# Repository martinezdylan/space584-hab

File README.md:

# space584-hab
A repository for the UM squad in SPACE 584 for High Altitude Baloon (Team KGB - Kewl Girls and Boiz).

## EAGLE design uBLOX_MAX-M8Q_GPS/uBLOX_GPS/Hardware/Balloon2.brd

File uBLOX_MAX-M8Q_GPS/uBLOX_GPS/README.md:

# Balloon Mission Computer 4

Ido Roseman

bmc4 is an attemp to use the Raspberry Pi as a mission computer for high altitude balloons.
this is a work in progress so documentation is minimal and bugs galor

## You can find me at
idoroseman.com
ido.roseman@gmail.com

## contribution
more code is needed. you are welcome to participate

## License
All of the code contained here is licensed by T.B.D

## Credits

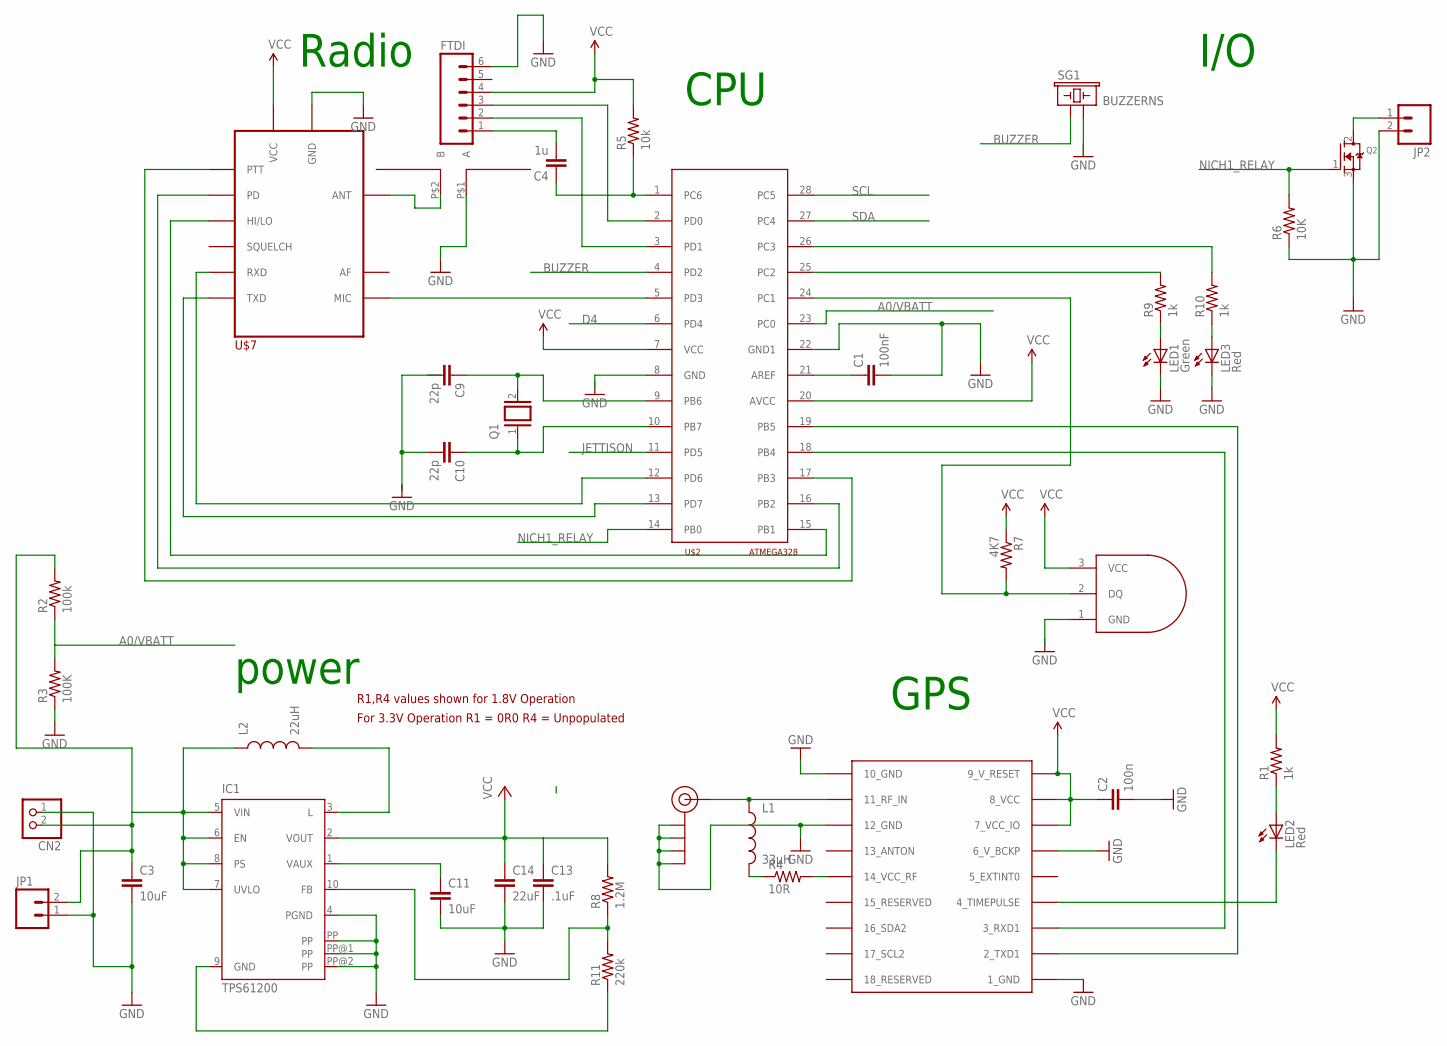
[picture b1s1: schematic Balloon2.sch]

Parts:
C1: 100nF; 0805
C2: 100n; 0805
C3, C11: 10uF; 0805
C4: 1u; 0805
C9, C10: 22p; 0805
C13: .1uF; 0805
C14: 22uF; 0805
CN2: JST_2PIN-SMT-RA; JST-PH-2-SMT-RA
FTDI: M06SIP; 1X06
IC1: TPS61200; S-PDSO-N10
J$2: SMA_EDGE; SMA-EDGE
JP1, JP2: M02PTH; 1X02
L1: 33µH; 0805
L2: 22uH; INDUCTOR-SRP4020
LED1: Green; CHIP-LED0805
LED2, LED3: Red; CHIP-LED0805
Q1: XTAL/S; QS
Q2: MOSFET-NGDS_TO220V; TO220V
R1, R9, R10: 1k; 0805
R2: 100k; 0805
R3: 100K; 0805
R4: 10R; 0805
R5: 10k; 0805
R6: 10K; 0805
R7: 4K7; 0805
R8: 1.2M; 0805
R11: 220k; 0805
SG1: BUZZERNS; BUZZER-12MM-NS
U$1: UBLOX_MAX
U$2: ATMEGA328; DIL28
U$3: DS18B20; TO-92
U$4: SOLDER-DIPOLE; SOLDERED-DIPOLE-5MM
U$7: DORJI

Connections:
A0/VBATT: R2.1, R3.2, U$2.23 (PC0)
BUZZER: SG1.+ (1), U$2.4 (PD2)
D4: U$2.6 (PD4)
GND: C1.2, C2.2, C3.2, C11.2, C13.2, C14.2, CN2.1 (2), FTDI.6, IC1.4 (PGND), IC1.PP, IC1.PP@1 (PP), IC1.PP@2 (PP), J$2.GND@0 (GND), J$2.GND@1 (GND), J$2.GND@2 (GND), J$2.GND@3 (GND), JP1.1, JP2.2, LED1.C, LED3.C, Q2.3 (S), R3.1, R6.1, U$1.1_GND, U$1.6_V_BCKP, U$1.10_GND, U$1.12_GND, U$2.22 (GND1), U$4.P$1 (A), U$7.P$9 (GND), U$7.P$10 (GND)
JETTISON: U$2.11 (PD5)
unnamed: U$2.5 (PD3), U$7.P$18 (MIC)
unnamed: C4.2, FTDI.1
unnamed: C4.1, R5.1, U$2.1 (PC6)
unnamed: J$2.SIG (SIGNAL), L1.1, U$1.11_RF_IN
unnamed: IC1.3 (L), L2.P$2 (2)
unnamed: U$4.P$2 (B), U$7.P$12 (ANT)
unnamed: LED2.A, R1.1
unnamed: FTDI.3, U$2.2 (PD0)
unnamed: FTDI.2, U$2.3 (PD1)
unnamed: LED2.C, U$1.4_TIMEPULSE
unnamed: LED1.A, R9.1
unnamed: LED3.A, R10.1
unnamed: L1.2, R4.1
unnamed: R4.2, U$1.14_VCC_RF
unnamed: C9.1, Q1.2, U$2.9 (PB6)
unnamed: C10.1, Q1.1, U$2.10 (PB7)
unnamed: U$1.3_RXD1, U$2.18 (PB4)
unnamed: U$2.12 (PD6), U$7.P$16 (RXD)
unnamed: U$2.13 (PD7), U$7.P$17 (TXD)
unnamed: U$2.15 (PB1), U$7.P$7 (HI/LO)
unnamed: U$2.16 (PB2), U$7.P$6 (PD)
unnamed: U$2.17 (PB3), U$7.P$5 (PTT)
unnamed: C3.1, CN2.2 (1), IC1.5 (VIN), IC1.6 (EN), IC1.7 (UVLO), IC1.8 (PS), JP1.2, L2.P$1 (1), R2.2
unnamed: C1.1, U$2.21 (AREF)
unnamed: U$1.2_TXD1, U$2.19 (PB5)
unnamed: R10.2, U$2.26 (PC3)
unnamed: R9.2, U$2.25 (PC2)
unnamed: R7.2, U$2.24 (PC1), U$3.2 (DQ)
unnamed: JP2.1, Q2.2 (D)
unnamed: IC1.10 (FB), R8.1, R11.2
unnamed: C11.1, IC1.1 (VAUX)
unnamed: IC1.9 (GND), R11.1
NICH1_RELAY: Q2.1 (G), R6.2, U$2.14 (PB0)
SCL: U$2.28 (PC5)
SDA: U$2.27 (PC4)
VCC: C2.1, C13.1, C14.1, FTDI.4, IC1.2 (VOUT), R1.2, R5.2, R7.1, R8.2, U$1.7_VCC_IO, U$1.8_VCC, U$1.9_V_RESET, U$2.7 (VCC), U$2.20 (AVCC), U$3.3 (VCC), U$7.P$8 (VCC)

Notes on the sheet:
R1,R4 values shown for 1.8V Operation
For 3.3V Operation R1 = 0R0 R4 = Unpopulated
GPS
Radio
power
CPU
I/O

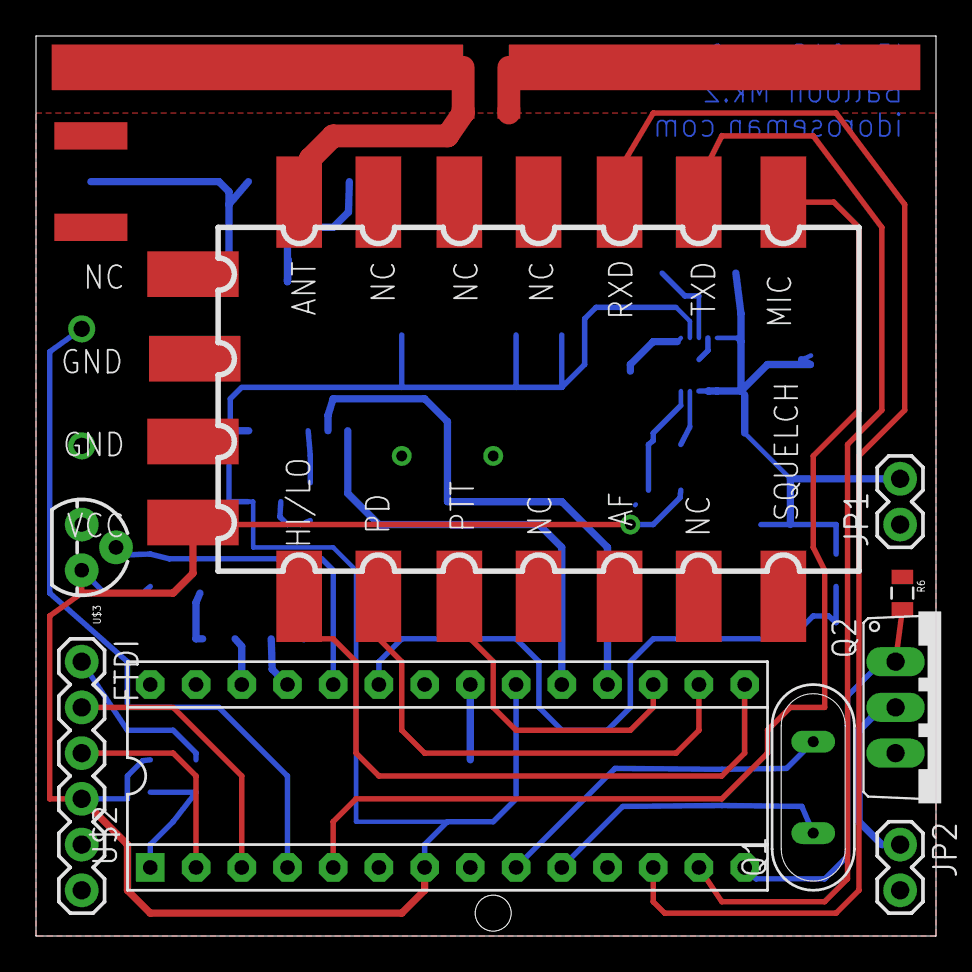
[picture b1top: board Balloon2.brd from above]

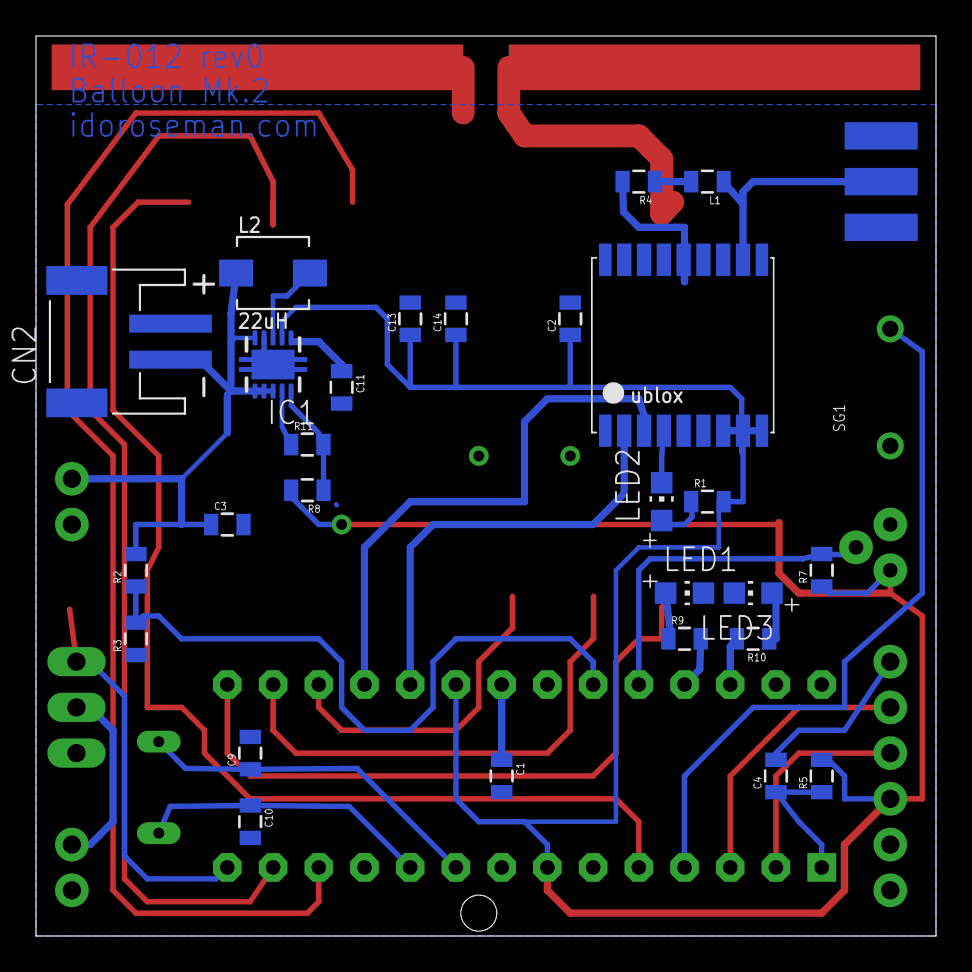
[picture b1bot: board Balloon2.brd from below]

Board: 2 copper layers, 50.0 x 50.0 mm, 39 parts (29 on the bottom side), 37 nets.

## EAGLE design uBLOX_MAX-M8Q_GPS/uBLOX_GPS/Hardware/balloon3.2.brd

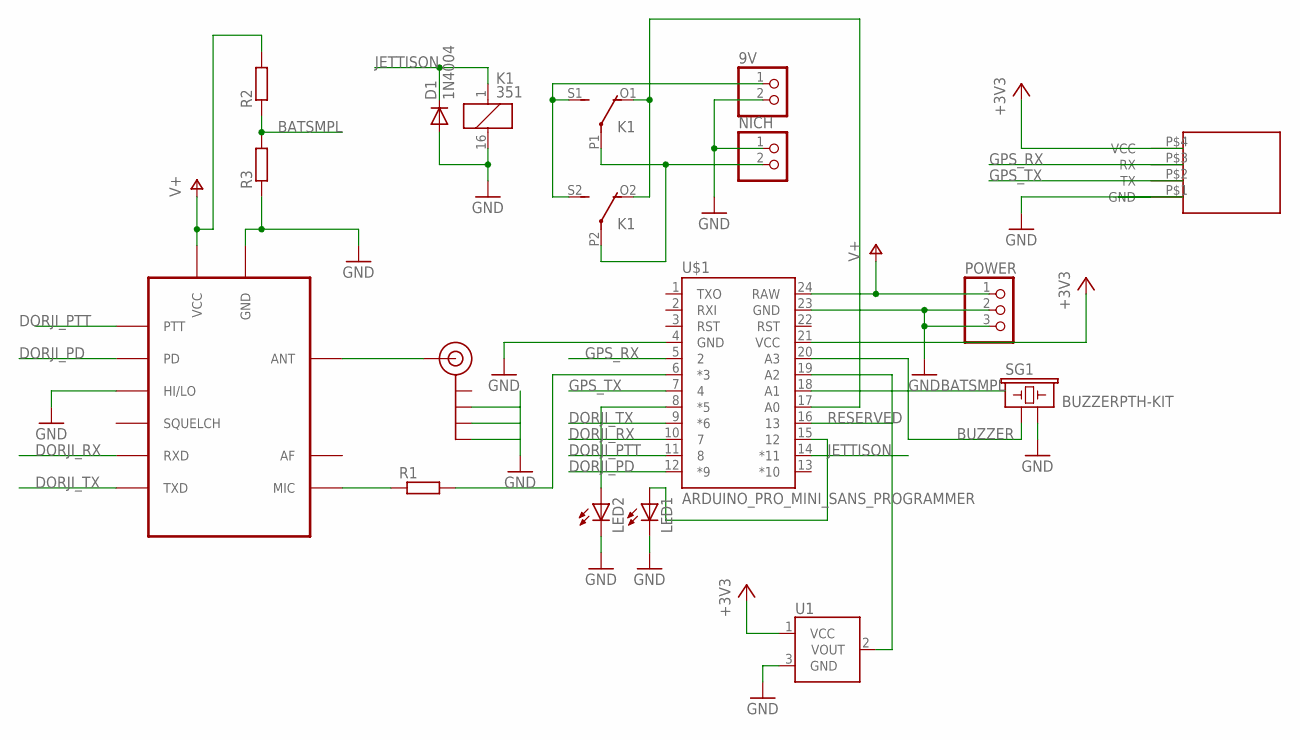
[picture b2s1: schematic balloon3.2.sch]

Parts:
9V: PINHD-1X2; 1X02
D1: 1N4004; DO41-10
J$1: SMA_EDGE; SMA-EDGE
K1: 351
LED1, LED2: LED3MM
NICH: PINHD-1X2; 1X02
POWER: PINHD-1X3; 1X03
R1, R2, R3: R-EU_0204/7; 0204/7
SG1: BUZZERPTH-KIT; BUZZER-12MM-KIT
U1: TMP36GT9; TO-92
U$1: ARDUINO_PRO_MINI_SANS_PROGRAMMER; ARDUINO_PRO_MINI
U$2: DORJI
U$3: NEO-6M-MODULE

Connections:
+3V3: U1.1 (VCC), U$1.21 (VCC), U$3.P$4 (VCC)
BATSMPL: R2.1, R3.2, U$1.18 (A1)
BUZZER: SG1.+ (1), U$1.20 (A3)
DORJI_PD: U$1.12 (*9), U$2.P$6 (PD)
DORJI_PTT: U$1.11 (8), U$2.P$5 (PTT)
DORJI_RX: U$1.10 (7), U$2.P$16 (RXD)
DORJI_TX: U$1.9 (*6), U$2.P$17 (TXD)
GND: 9V.2, D1.A, J$1.GND@1 (GND), J$1.GND@2 (GND), J$1.GND@3 (GND), K1.16 (2), LED1.K (C), LED2.K (C), NICH.1, POWER.2, POWER.3, R3.1, SG1.- (2), U1.3 (GND), U$1.4 (GND), U$1.23 (GND), U$2.P$7 (HI/LO), U$2.P$9 (GND), U$2.P$10 (GND), U$3.P$1 (GND)
GPS_RX: U$1.5 (2), U$3.P$3 (RX)
GPS_TX: U$1.7 (4), U$3.P$2 (TX)
JETTISON: D1.C, K1.1, U$1.14 (*11)
unnamed: R1.2, U$1.6 (*3)
unnamed: R1.1, U$2.P$18 (MIC)
unnamed: J$1.SIG (SIGNAL), U$2.P$12 (ANT)
unnamed: K1.P1, K1.P2, NICH.2
unnamed: LED2.A, U$1.8 (*5)
unnamed: 9V.1, K1.S1 (S), K1.S2 (S)
unnamed: K1.O1 (O), K1.O2 (O), U$1.17 (A0)
unnamed: U1.2 (VOUT), U$1.19 (A2)
unnamed: LED1.A, U$1.15 (12)
RESERVED: U$1.16 (13)
V+: POWER.1, R2.2, U$1.24 (RAW), U$2.P$8 (VCC)

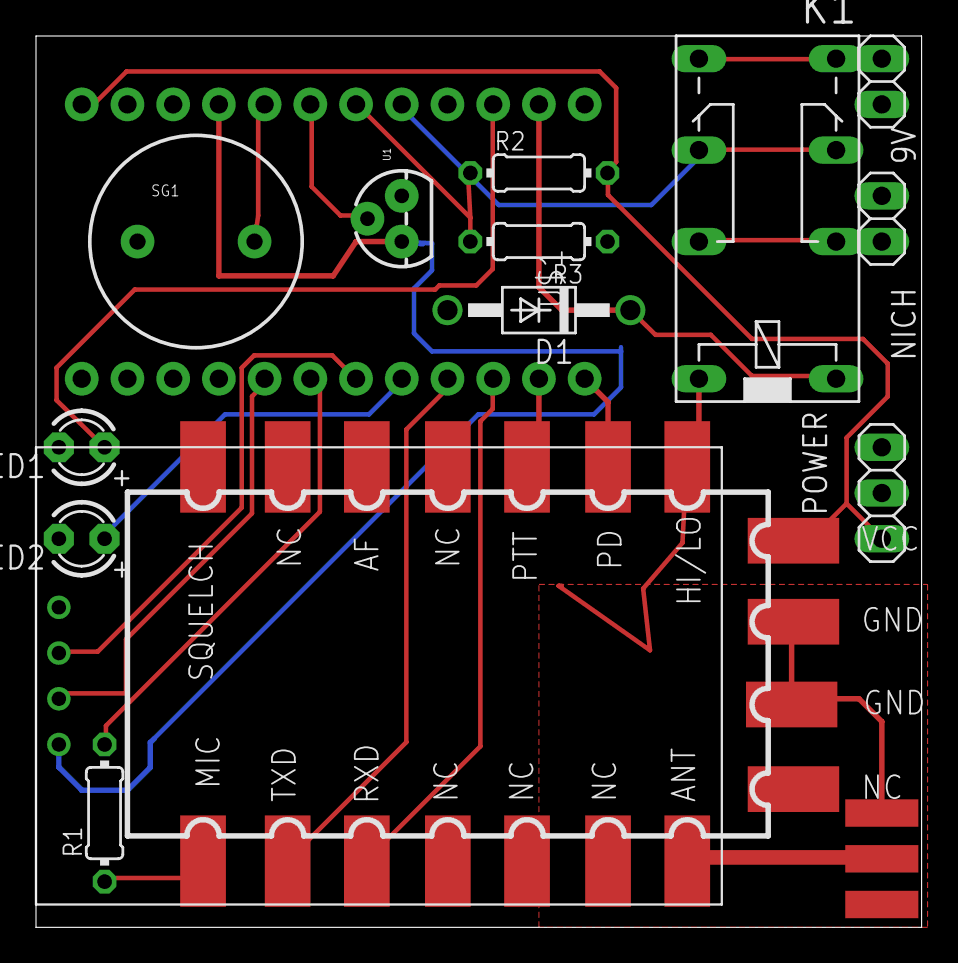
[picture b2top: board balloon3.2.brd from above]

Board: 2 copper layers, 49.2 x 49.5 mm, 16 parts (0 on the bottom side), 21 nets.

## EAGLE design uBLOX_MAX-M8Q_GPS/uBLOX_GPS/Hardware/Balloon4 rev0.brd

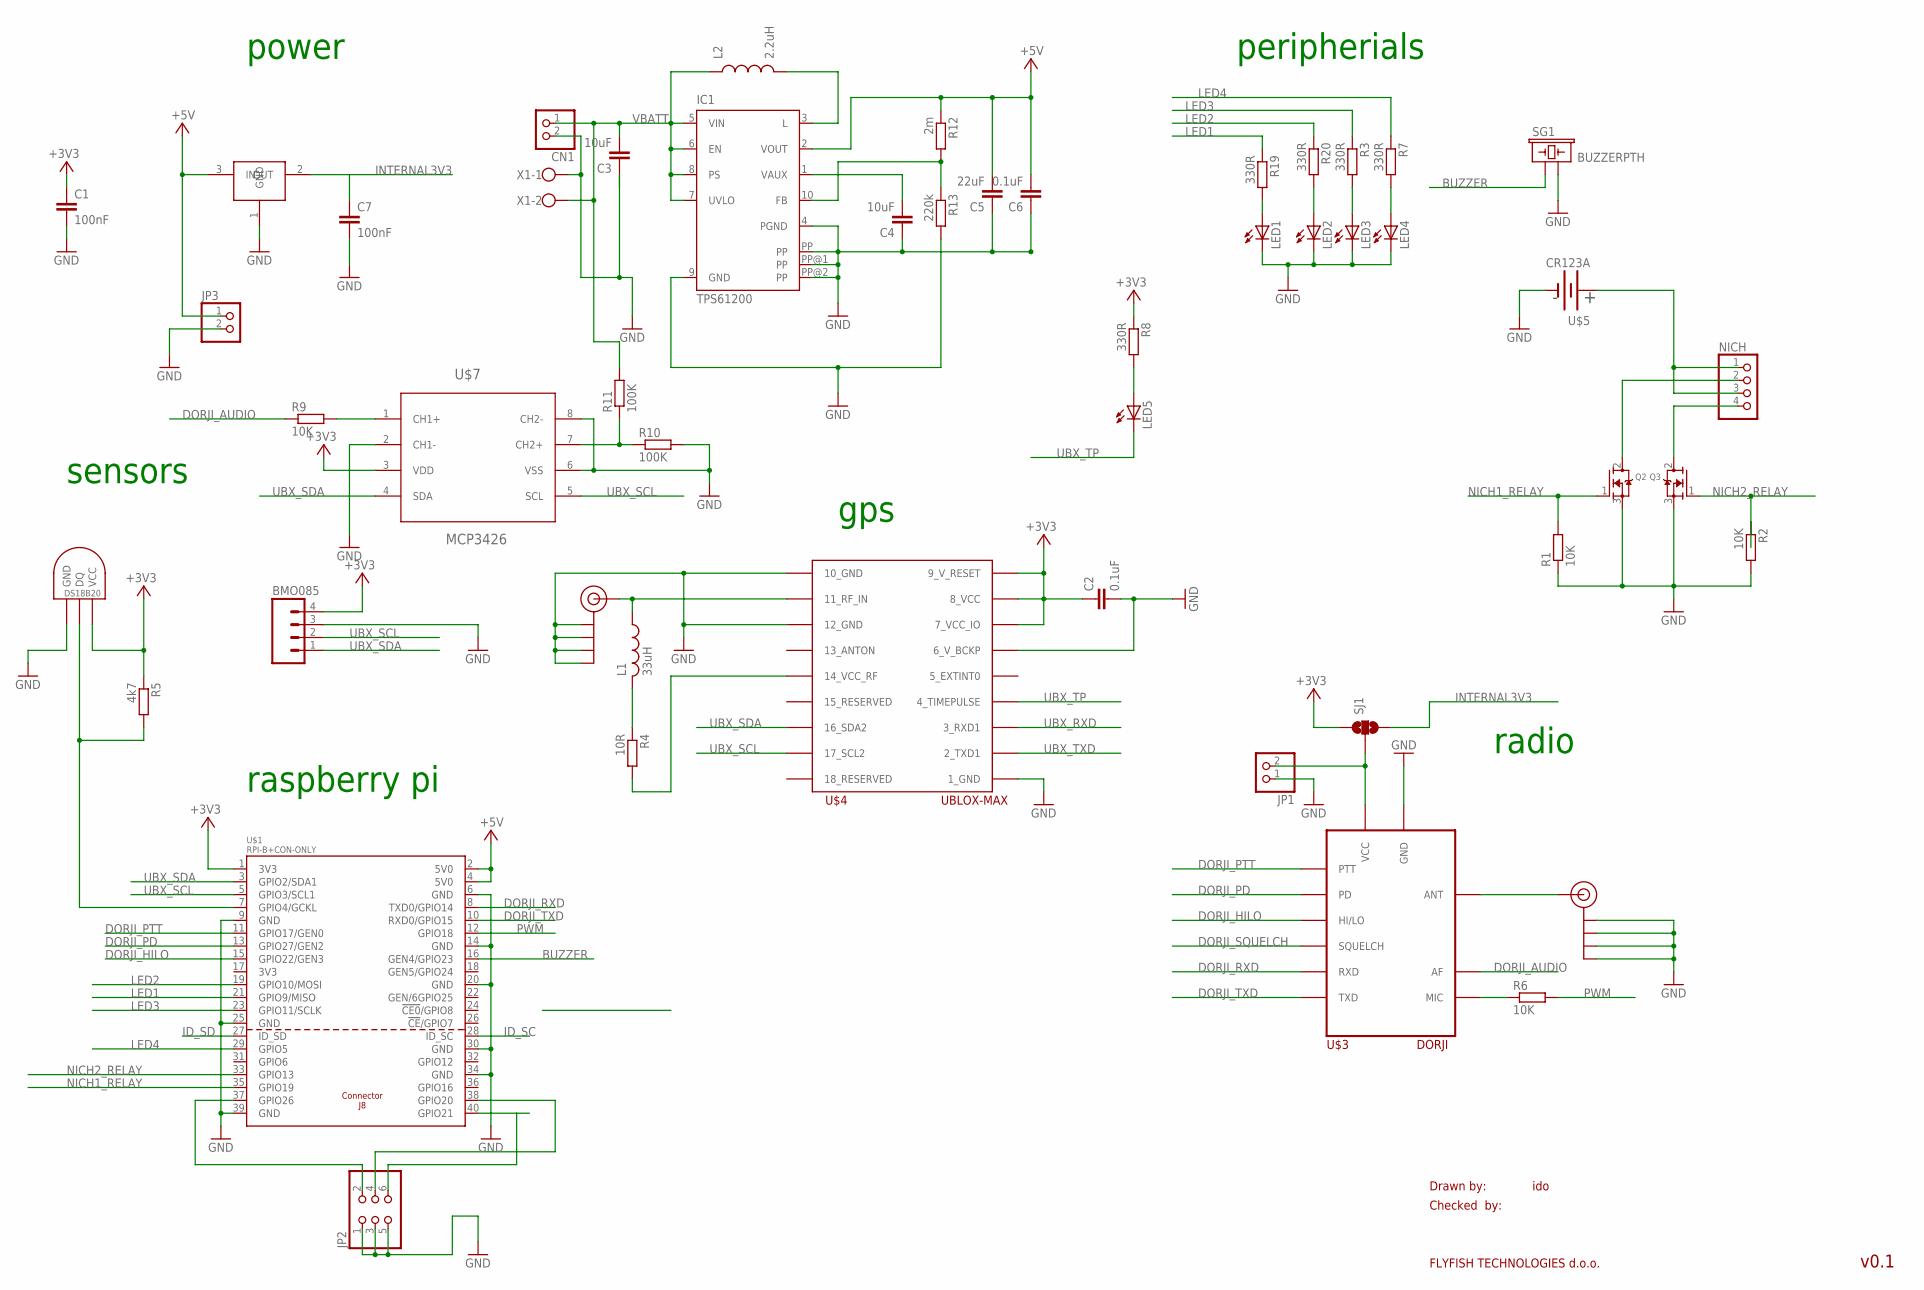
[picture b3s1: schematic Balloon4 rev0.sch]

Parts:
BMO085: M04PTH; 1X04
C1, C7: 100nF; C0805K
C2, C6: 0.1uF; C0805K
C3, C4: 10uF; C0805K
C5: 22uF; C0805K
CN1: JST_2PIN-SMT-RA; JST-PH-2-SMT-RA
IC1: TPS61200; S-PDSO-N10
J$1, J$2: SMA_EDGE; SMA-EDGE
JP1, JP3: PINHD-1X2; 1X02
JP2: PINHD-2X3; 2X03
L1: 33uH; M0805
L2: 2.2uH; INDUCTOR-SRP4020
LED1, LED2, LED3, LED4, LED5: LEDCHIP-LED0805; CHIP-LED0805
NICH: PINHD-1X4; 1X04
Q2, Q3: MOSFET-NGDS_TO220V; TO220V
R1, R2, R6, R9: 10K; M0805
R3, R7, R8, R19, R20: 330R; M0805
R4: 10R; M0805
R5: 4k7; M0805
R10, R11: 100K; M0805
R12: 2m; M0805
R13: 220k; M0805
SG1: BUZZERPTH; BUZZER-12MM
SJ1: SOLDERJUMPER_2WAYPASTE1&2; SJ_3_PASTE1&2
U$1: RPI-B+CON-ONLY; RPI-CON-B+
U$2: NCP1117; SOT223
U$3: DORJI
U$4: UBLOX-MAX
U$5: CR123A; CR123A_HOLDER
U$6: DS1820TO92; DS1820
U$7: MCP3426; SOIC127P600X175-8N
X1: W237-102

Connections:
+3V3: BMO085.4, C1.1, C2.1, R5.1, R8.1, SJ1.1, U$1.1 (3V3), U$4.7_VCC_IO, U$4.8_VCC, U$4.9_V_RESET, U$6.VDD (VCC), U$7.3 (VDD)
+5V: C5.2, C6.2, IC1.2 (VOUT), JP3.1, R12.1, U$1.2 (5V0), U$1.4 (5V0), U$2.3 (IN)
BUZZER: SG1.+ (1), U$1.16 (GEN4/GPIO23)
DORJI_AUDIO: R9.1, U$3.P$3 (AF)
DORJI_HILO: U$1.15 (GPIO22/GEN3), U$3.P$7 (HI/LO)
DORJI_PD: U$1.13 (GPIO27/GEN2), U$3.P$6 (PD)
DORJI_PTT: U$1.11 (GPIO17/GEN0), U$3.P$5 (PTT)
DORJI_RXD: U$1.8 (TXD0/GPIO14), U$3.P$16 (RXD)
DORJI_SQUELCH: U$3.P$1 (SQUELCH)
DORJI_TXD: U$1.10 (RXD0/GPIO15), U$3.P$17 (TXD)
GND: BMO085.3, C1.2, C2.2, C3.1, C4.1, C5.1, C6.1, C7.2, CN1.2 (1), IC1.4 (PGND), IC1.9 (GND), IC1.PP, IC1.PP@1 (PP), IC1.PP@2 (PP), J$1.GND@0 (GND), J$1.GND@1 (GND), J$1.GND@2 (GND), J$1.GND@3 (GND), J$2.GND@0 (GND), J$2.GND@1 (GND), J$2.GND@2 (GND), J$2.GND@3 (GND), JP1.1, JP2.1, JP2.3, JP2.5, JP3.2, LED1.C, LED2.C, LED3.C, LED4.C, Q2.3 (S), Q3.3 (S), R1.1, R2.2, R10.2, R13.2, SG1.- (2), U$1.6 (GND), U$1.9 (GND), U$1.14 (GND), U$1.20 (GND), U$1.25 (GND), U$1.30 (GND), U$1.34 (GND), U$1.39 (GND), U$2.1 (GND), U$3.P$9 (GND), U$3.P$10 (GND), U$4.1_GND, U$4.6_V_BCKP, U$4.10_GND, U$4.12_GND, U$5.-, U$6.GND, U$7.2 (CH1-), U$7.6 (VSS), U$7.8 (CH2-), X1.1
ID_SC: U$1.28 (ID_SC)
ID_SD: U$1.27 (ID_SD)
INTERNAL3V3: C7.1, SJ1.3, U$2.2 (OUT)
LED1: R19.1, U$1.21 (GPIO9/MISO)
LED2: R20.1, U$1.19 (GPIO10/MOSI)
LED3: R3.1, U$1.23 (GPIO11/SCLK)
LED4: R7.1, U$1.29 (GPIO5)
unnamed: R6.1, U$3.P$18 (MIC)
unnamed: R5.2, U$1.7 (GPIO4/GCKL), U$6.DQ
unnamed: J$2.SIG (SIGNAL), U$3.P$12 (ANT)
unnamed: J$1.SIG (SIGNAL), L1.1, U$4.11_RF_IN
unnamed: L1.2, R4.1
unnamed: R4.2, U$4.14_VCC_RF
unnamed: JP1.2, SJ1.2, U$3.P$8 (VCC)
unnamed: NICH.2, Q2.2 (D)
unnamed: IC1.3 (L), L2.P$2 (2)
unnamed: NICH.4, Q3.2 (D)
unnamed: JP2.2, U$1.37 (GPIO26)
unnamed: LED3.A, R3.2
unnamed: JP2.6, U$1.40 (GPIO21)
unnamed: JP2.4, U$1.38 (GPIO20)
unnamed: LED5.A, R8.2
unnamed: LED4.A, R7.2
unnamed: R10.1, R11.1, U$7.7 (CH2+)
unnamed: R9.2, U$7.1 (CH1+)
unnamed: R12.2, R13.1
unnamed: C4.2, IC1.1 (VAUX)
unnamed: NICH.1, NICH.3, U$5.+
unnamed: LED2.A, R20.2
unnamed: LED1.A, R19.2
NICH1_RELAY: Q2.1 (G), R1.2, U$1.35 (GPIO19)
NICH2_RELAY: Q3.1 (G), R2.1, U$1.33 (GPIO13)
PWM: R6.2, U$1.12 (GPIO18)
UBX_RXD: U$4.3_RXD1
UBX_SCL: BMO085.2, U$1.5 (GPIO3/SCL1), U$4.17_SCL2, U$7.5 (SCL)
UBX_SDA: BMO085.1, U$1.3 (GPIO2/SDA1), U$4.16_SDA2, U$7.4 (SDA)
UBX_TP: LED5.C, U$4.4_TIMEPULSE
UBX_TXD: U$4.2_TXD1
VBATT: C3.2, CN1.1 (2), IC1.5 (VIN), IC1.6 (EN), IC1.7 (UVLO), IC1.8 (PS), L2.P$1 (1), R11.2, X1.2

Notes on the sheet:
Drawn by:
Checked by:
FLYFISH TECHNOLOGIES d.o.o.
ido
v0.1
power
peripherials
radio
gps
raspberry pi
sensors

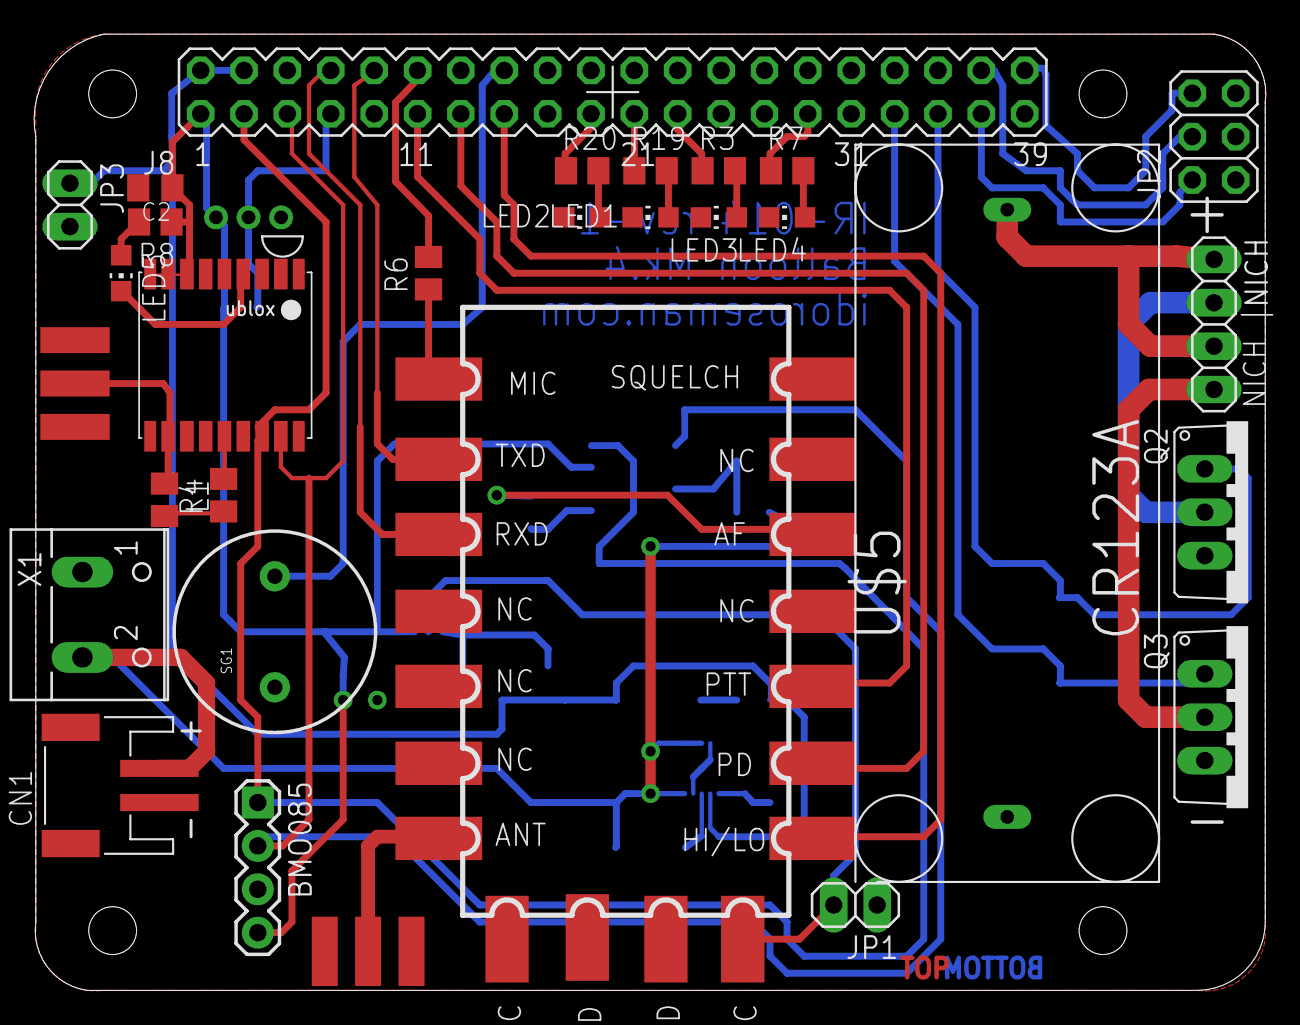
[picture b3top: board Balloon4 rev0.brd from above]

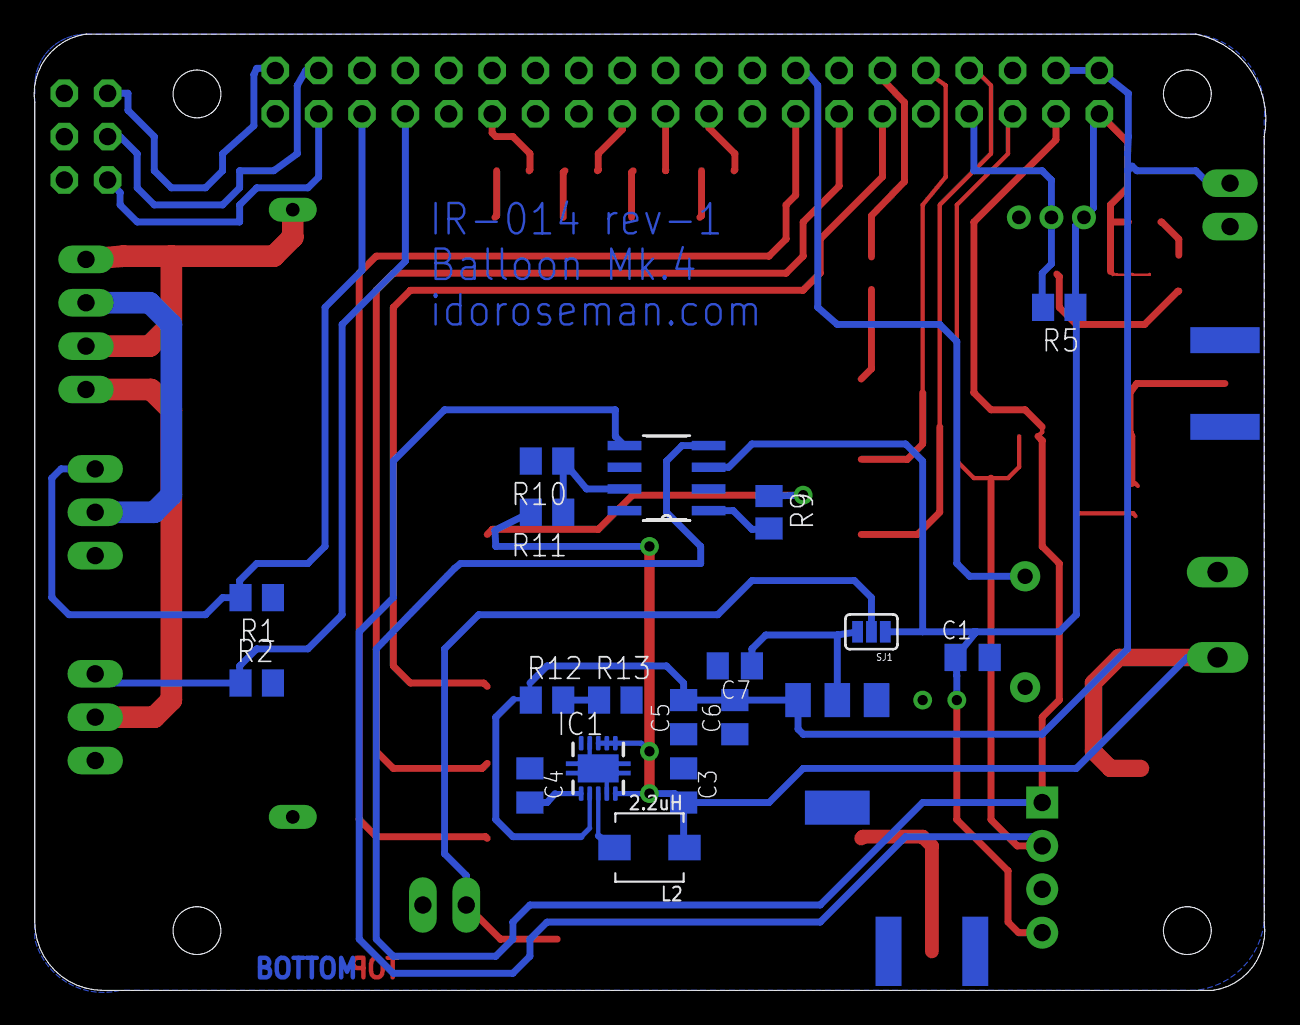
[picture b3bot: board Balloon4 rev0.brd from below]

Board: 2 copper layers, 72.1 x 56.0 mm, 50 parts (19 on the bottom side), 45 nets.

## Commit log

2020-02-06 initial push
2020-02-11 Added lab 1 compiled code
2020-02-11 added GPS code changes
2020-02-11 removed old gps, added new python
2020-02-11 Modified lab1 and thermistor code
2020-02-12 updated lab1_code, creates csv and appends
2020-02-17 Fixed thermistor code
2020-02-17 added timestamp + thermistor to lab1_code
2020-02-18 Fixed lab1 code and added output file
2020-02-18 updates to headers and added altitutde
2020-02-19 thermistor changes :(
2020-02-20 Edited lab 1 code
2020-02-20 spelling update
2020-02-24 Edited gps and calibration stuff
2020-02-24 lab1 2hr output
2020-02-24 finalized lab1 2hr csv
2020-02-25 renamed labfile, to keep 2hr
2020-02-25 adding new gps code
2020-02-25 pushing lab2 code
2020-02-25 small code update for loop
2020-02-25 added logger for writing
2020-02-25 final update
2020-02-25 quick fix
2020-02-25 adding lab2 walkaround
2020-03-12 Updated bno055 library

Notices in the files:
parts and their libraries:
SparkFun-Electromechanical: Licensing: Creative Commons ShareAlike 4.0 International - https://creativecommons.org/licenses/by-sa/4.0
